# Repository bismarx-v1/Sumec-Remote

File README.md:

# IR Remote for SUMEC MiniSumo robot

## Description
Sumec-Remote repo contains files that are forked from p1rse as well as our own software, hardware and documentation for IR MiniSumo remote.

## Contents

- **-CODE-** Contains flashed code on the remote.
  
- **-DOCS-** Includes documentation about the project.

- **-PCB-** Includes schematics, bill of materials and pcb files. Schematic and PCBs are created using KiCAD.

## Contact
If you have any questions, suggestions, or issues regarding this project, please feel free to contact us: 

Email - savvapopov1804@gmail.com
LinkedIn - www.linkedin.com/in/popovsavvaprosek/

And follow us on the social media! 
Instagram - @sumec_minisumo_bot

**Sending love, from Czech Republic!**

## For information about the start module and its usage visit: http://www.startmodule.com

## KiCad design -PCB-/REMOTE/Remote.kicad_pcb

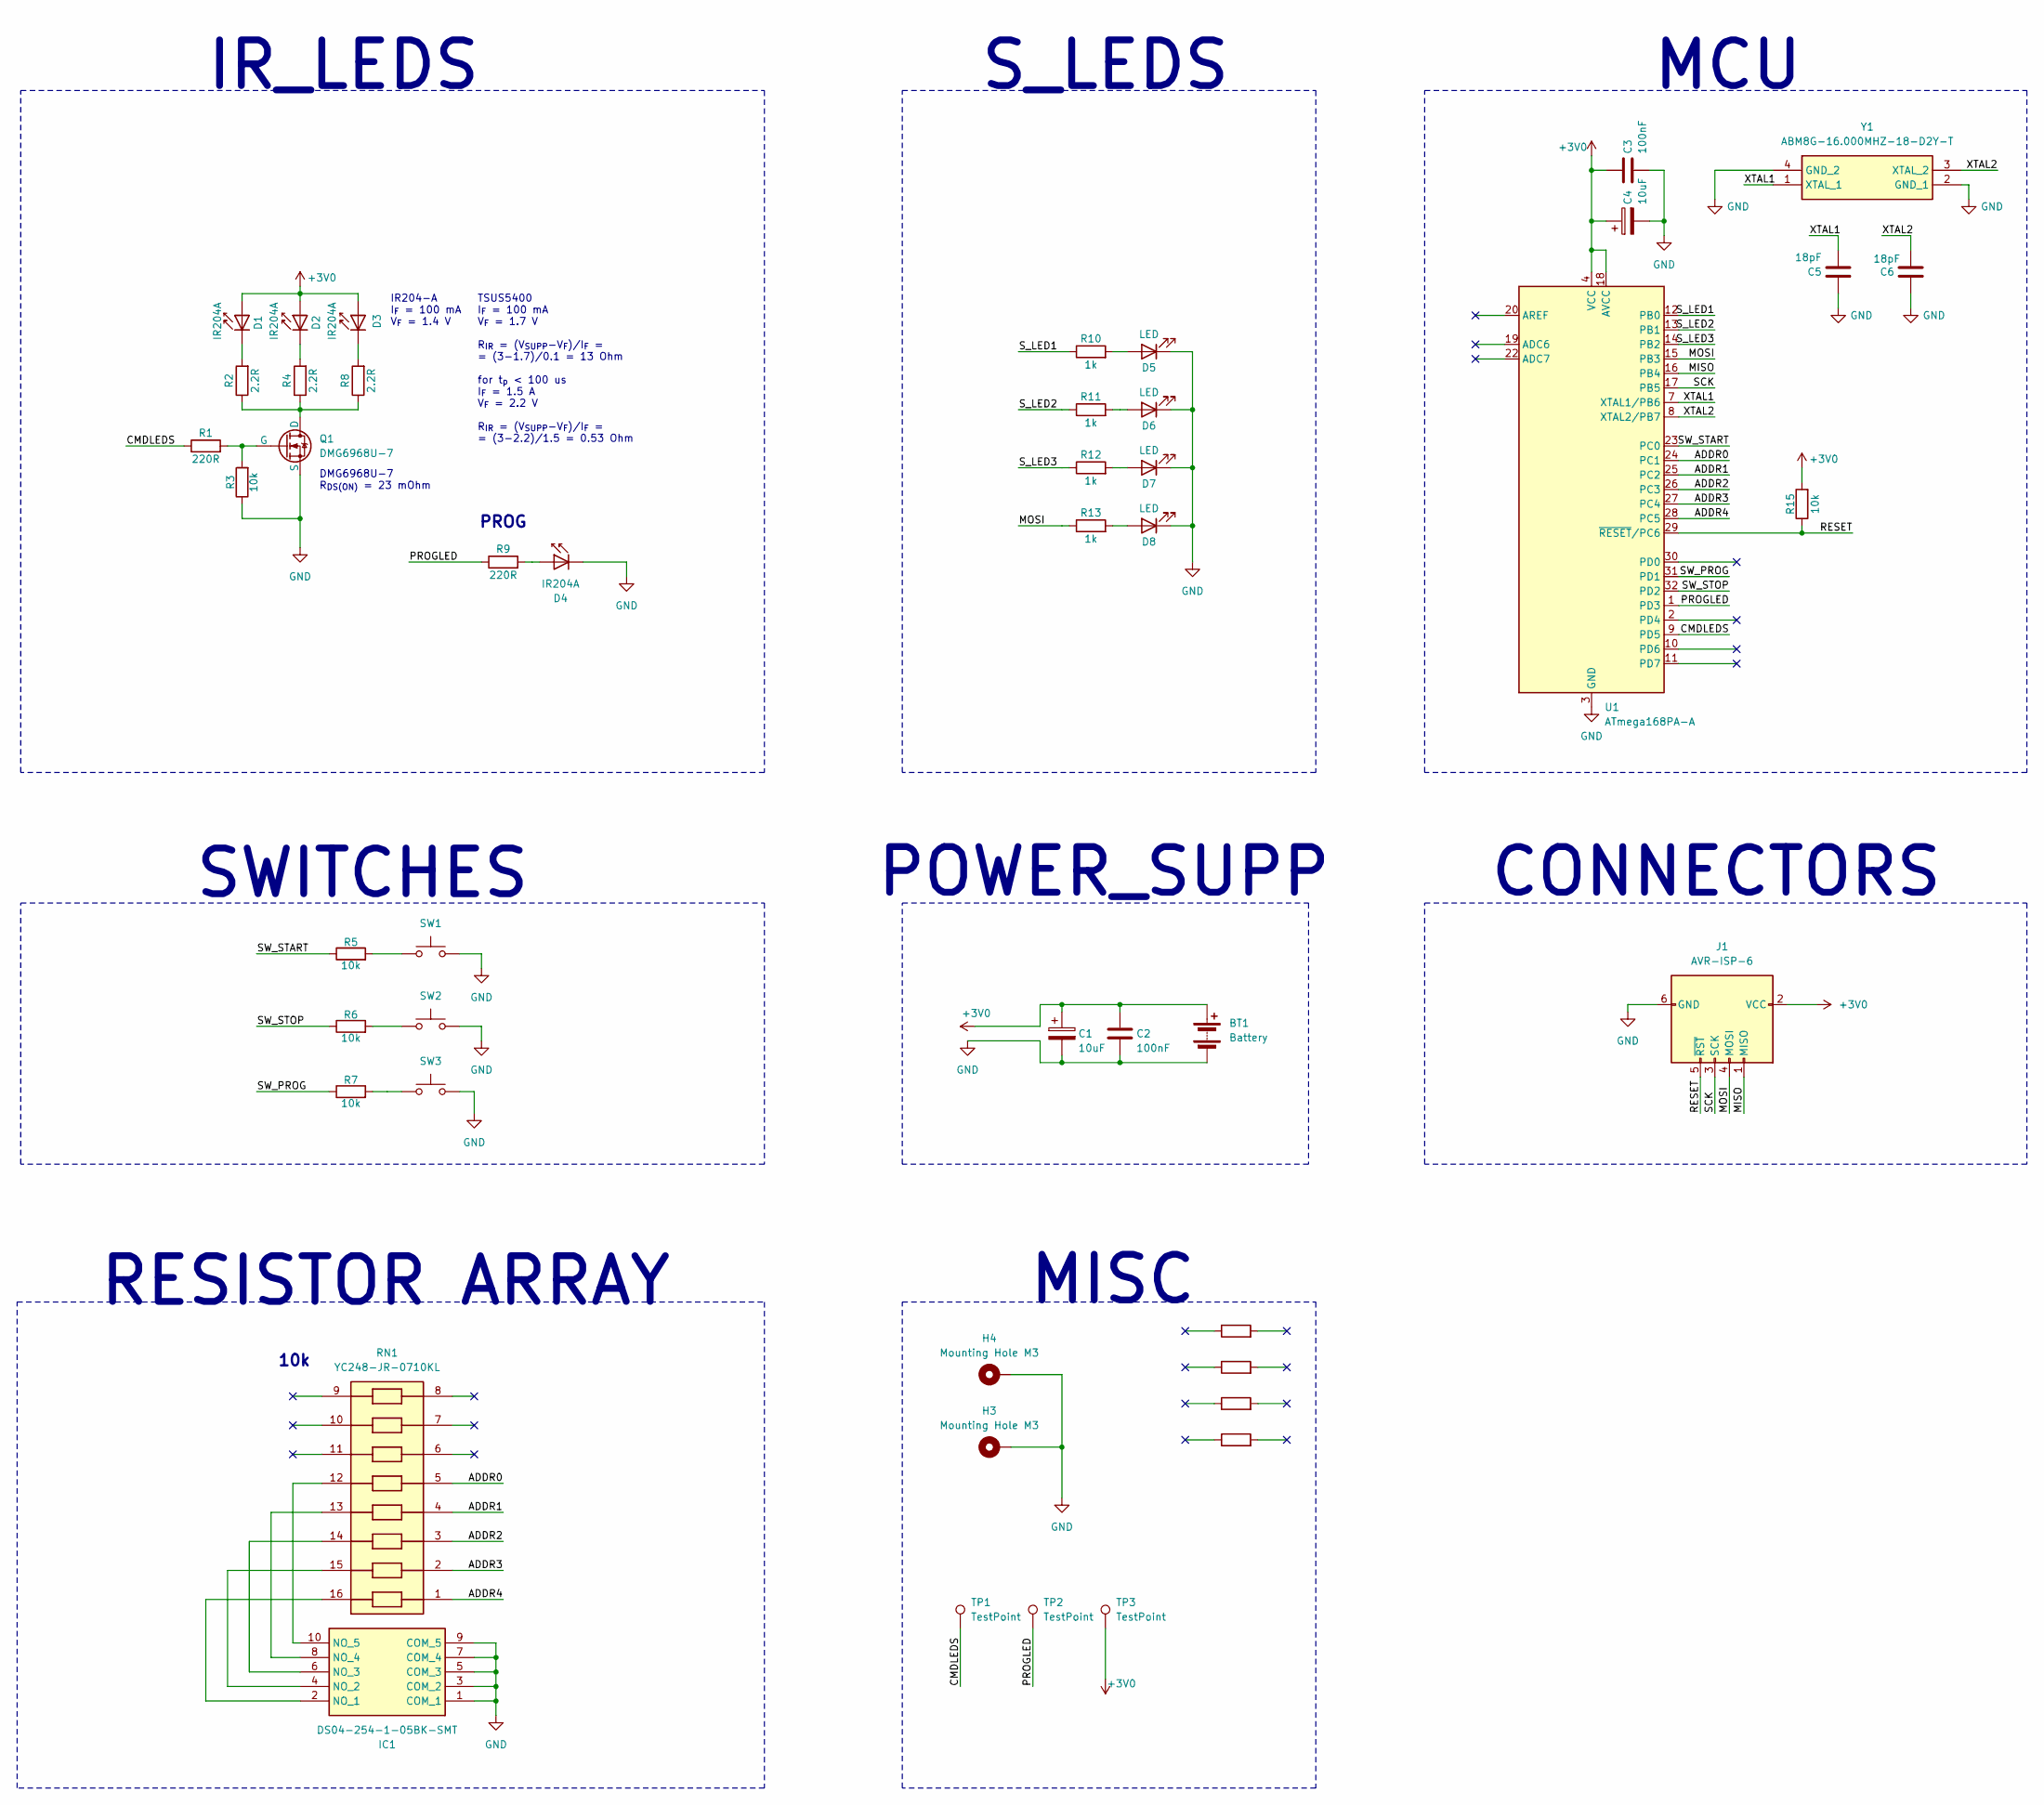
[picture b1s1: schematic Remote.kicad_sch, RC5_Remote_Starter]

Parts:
BT1: Battery; BatteryHolder_Keystone_2462_2xAA - no holes
C1, C4: 10uF; CP_EIA-3216-18_Kemet-A_Pad1.58x1.35mm_HandSolder
C2, C3: 100nF; C_0805_2012Metric_Pad1.18x1.45mm_HandSolder
C5, C6: 18pF; C_0805_2012Metric_Pad1.18x1.45mm_HandSolder
D1, D3: IR204A; LED_D3.0mm_Horizontal_O3.81mm_Z10.0mm_no_silk
D2: IR204A; LED_D3.0mm_Horizontal_O3.81mm_Z10.0mm_flipped_no_silk
D4: IR204A; LED_D3.0mm_Horizontal_O3.81mm_Z10.0mm_flipped
D5, D6, D7, D8: LED; LED_0805_2012Metric_Pad1.15x1.40mm_HandSolder
H3, H4: Mounting Hole M3; MountingHole_3.2mm_M3_Pad_Via
IC1: DS04-254-1-05BK-SMT; dip_switch; Mouser Part Number 490-DS04254105BK-SMT
J1: AVR-ISP-6; PinHeader_2x03_P2.54mm_Vertical
Q1: DMG6968U-7; SOT-23-3
R1, R9: 220R; R_0805_2012Metric_Pad1.20x1.40mm_HandSolder
R2, R4, R8: 2.2R; R_0805_2012Metric_Pad1.20x1.40mm_HandSolder
R3, R5, R6, R7, R15: 10k; R_0805_2012Metric_Pad1.20x1.40mm_HandSolder
R10, R11, R12, R13: 1k; R_0805_2012Metric_Pad1.20x1.40mm_HandSolder
R14: R; purosidenegative
R16: R; SPS LOGO
R17: R; boi
R18: R; Logo
RN1: YC248-JR-0710KL; resistor_array; Mouser Part Number 603-YC248-JR-0710KL
SW1, SW2, SW3: SW_Push; SW_PUSH_6mm
TP1, TP2, TP3: TestPoint; TestPoint_Pad_D1.5mm
U1: ATmega168PA-A; TQFP-32_7x7mm_P0.8mm
Y1: ABM8G-16.000MHZ-18-D2Y-T; crystal_smd; Mouser Part Number 815-ABM8G-16-18D2Y

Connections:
+3V0: BT1.1 (+), C1.1, C2.1, C3.1, C4.1, D1.2 (A), D2.2 (A), D3.2 (A), J1.2 (VCC), R15.2, TP3.1, U1.4 (VCC), U1.6 (VCC), U1.18 (AVCC)
/ADDR0: RN1.5, U1.24 (PC1)
/ADDR1: RN1.4, U1.25 (PC2)
/ADDR2: RN1.3, U1.26 (PC3)
/ADDR3: RN1.2, U1.27 (PC4)
/ADDR4: RN1.1, U1.28 (PC5)
/CMDLEDS: R1.1, TP1.1, U1.9 (PD5)
/MISO: J1.1 (MISO), U1.16 (PB4)
/MOSI: J1.4 (MOSI), R13.1, U1.15 (PB3)
/PROGLED: R9.1, TP2.1, U1.1 (PD3)
/RESET: J1.5 (~RST), R15.1, U1.29 (~RESET/PC6)
/SCK: J1.3 (SCK), U1.17 (PB5)
/SW_PROG: R7.1, U1.31 (PD1)
/SW_START: R5.1, U1.23 (PC0)
/SW_STOP: R6.1, U1.32 (PD2)
/S_LED1: R10.1, U1.12 (PB0)
/S_LED2: R11.1, U1.13 (PB1)
/S_LED3: R12.1, U1.14 (PB2)
/XTAL1: C5.2, U1.7 (XTAL1/PB6), Y1.1 (XTAL_1)
/XTAL2: C6.2, U1.8 (XTAL2/PB7), Y1.3 (XTAL_2)
GND: BT1.2 (-), C1.2, C2.2, C3.2, C4.2, C5.1, C6.1, D4.1 (K), D5.1 (K), D6.1 (K), D7.1 (K), D8.1 (K), H3.1, H4.1, IC1.1 (COM_1), IC1.3 (COM_2), IC1.5 (COM_3), IC1.7 (COM_4), IC1.9 (COM_5), J1.6 (GND), Q1.3 (S), R3.1, SW1.2, SW2.2, SW3.2, U1.3 (GND), U1.5 (GND), U1.21 (GND), Y1.2 (GND_1), Y1.4 (GND_2)
unnamed: D1.1 (K), R2.2
unnamed: D2.1 (K), R4.2
unnamed: D3.1 (K), R8.2
unnamed: D4.2 (A), R9.2
unnamed: D5.2 (A), R10.2
unnamed: D6.2 (A), R11.2
unnamed: D7.2 (A), R12.2
unnamed: D8.2 (A), R13.2
unnamed: IC1.2 (NO_1), RN1.16
unnamed: IC1.4 (NO_2), RN1.15
unnamed: IC1.6 (NO_3), RN1.14
unnamed: IC1.8 (NO_4), RN1.13
unnamed: IC1.10 (NO_5), RN1.12
unnamed: Q1.1 (D), R2.1, R4.1, R8.1
unnamed: Q1.2 (G), R1.2, R3.2
unnamed: R5.2, SW1.1
unnamed: R6.2, SW2.1
unnamed: R7.2, SW3.1

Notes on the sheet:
MISC
MCU
IR204-A I_{F} = 100 mA V_{F} = 1.4 V
SWITCHES
10k
POWER_SUPP
RESISTOR ARRAY
TSUS5400 I_{F} = 100 mA V_{F} = 1.7 V R_{IR} = (V_{SUPP}-V_{F})/I_{F} = = (3-1.7)/0.1 = 13 Ohm for t_{p} < 100 us I_{F} = 1.5 A V_{F} = 2.2 V R_{IR} = (V_{SUPP}-V_{F})/I_{F} = = (3-2.2)/1.5 = 0.53 Ohm
S_LEDS
CONNECTORS
IR_LEDS
PROG
DMG6968U-7 R_{DS(ON)} = 23 mOhm

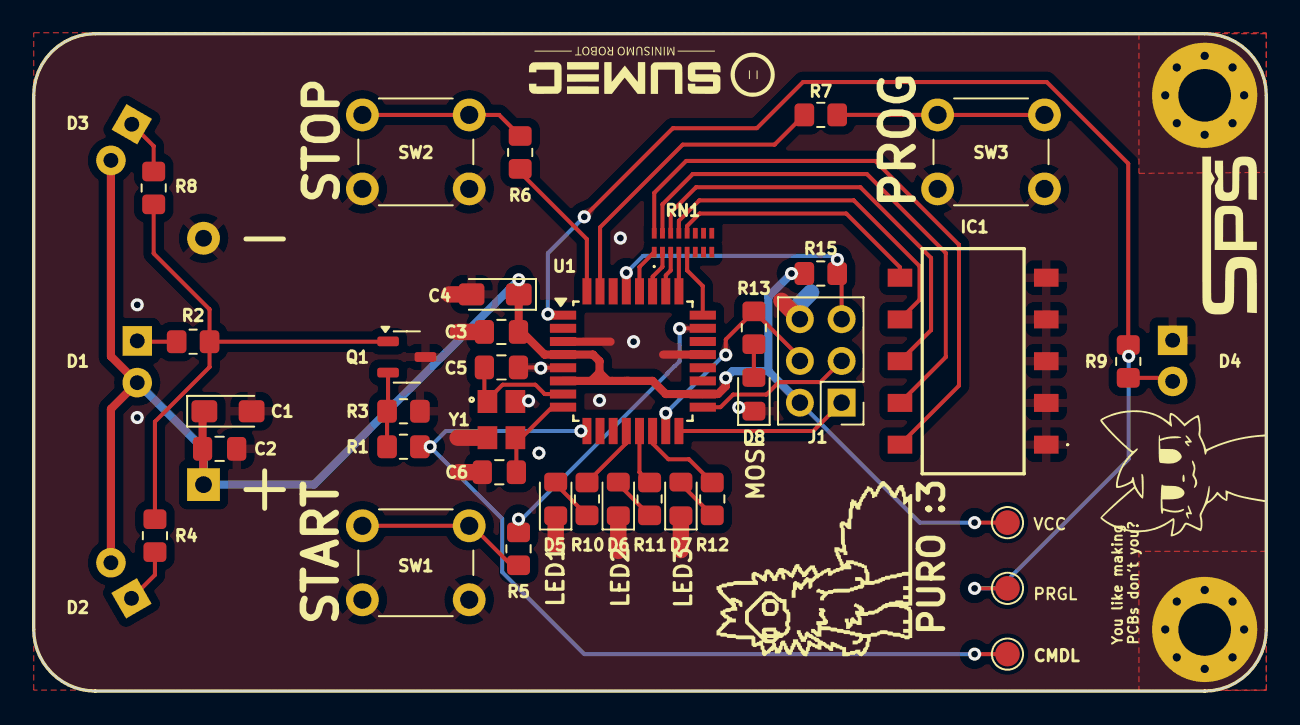
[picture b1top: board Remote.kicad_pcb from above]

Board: 2 copper layers, 75.0 x 40.0 mm, 47 parts (1 on the bottom side), 39 nets.

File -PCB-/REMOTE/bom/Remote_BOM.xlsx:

| Value | Link | Reserve | Quantity | Footprint
 | 10uF | 10uF, 16V, 1206, tantal, mouser | >30 | 2 | CP_EIA-3216-18_Kemet-A_Pad1.58x1.35mm_HandSolder
 | 100nF | 100nF, 16V, 0805, ceramic, mouser X7R | >80 | 2 | C_0805_2012Metric_Pad1.18x1.45mm_HandSolder
 | 18pF | 18pF, 16V, 0805, ceramic, mouser |  | 2 | C_0805_2012Metric_Pad1.18x1.45mm_HandSolder
 | 10k | 10k, 250mW, 0805, mouser |  | 5 | R_0805_2012Metric_Pad1.20x1.40mm_HandSolder
 | 1k | 1k. 500mW, 0805, mouser |  | 4 | R_0805_2012Metric_Pad1.20x1.40mm_HandSolder
 | 200R | 200R, 500mW, 0805, mouser |  | 2 | R_0805_2012Metric_Pad1.20x1.40mm_HandSolder
 | 2.2R | 2.2R, 500mW, 0805, mouser |  | 3 | R_0805_2012Metric_Pad1.20x1.40mm_HandSolder
 | YC248-JR-0710KL | 10k, 8x0402, mouser |  | 1 | resistor_array
 | LED | Yellow, Red, Green (NIO) | 8,8,18 | 4 | LED_0805_2012Metric_Pad1.15x1.40mm_HandSolder
 | IR204A | IR LED, 50mA, 1.3V, mouser |  | 4 | LED_D3.0mm_Horizontal_O3.81mm_Z10.0mm | Red LED, 20mA 1.9V, 0805, mouser
 | Crystal - ABM8G | 16 MHz, 18 pF, mouser |  | 1 | crystal_smd | Yellow LED, 20mA, 1.9V, 0805, mouser
 | DMG6968U-7 | NMOS, SOT23-3, mouser |  | 1 | TSOT-23-3_HandSoldering | Green-Yellow LED, 20mA, 1.9V, mouser
 | ATmega168PA-AU | TQFP-32, 1.8 - 5.5 [V], mouser |  | 1 | TQFP-32_7x7mm_P0.8mm
 | SW_Push | Height 8mm, Width 6mm, mouser |  | 3 | SW_PUSH_6mm
 | DS04-254-1-05BK-SMT | 5P, 2.54mm, DIP, mouser |  | 1 | dip_switch
 | Battery | Keystone_2462, 2xAA, mouser |  | 1 | BatteryHolder_Keystone_2462_2xAA - no holes
 | AVR-ISP-6 | GME |  | 1 | PinHeader_2x03_P2.54mm_Vertical
 | NIO - Not in order

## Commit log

2024-08-31 Copied from old repo
2024-09-05 Updated remote BOM
    Updated sumec remote idk what i updated but its different
2024-09-06 Forgot to save dummy file
2024-09-06 deletion of dummt txt
2024-09-16 dummy txt
2024-09-30 no chnage
2024-10-14 Schematic update
    Font update
2024-10-15 some 3 updates
2025-04-14 bom change
2025-07-17 starting module code
    colied from the main software repo. both of these repos are a mess.
